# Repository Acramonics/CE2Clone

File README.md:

Boss CE-2 Clone
===============

**Andrew Martin, September 2025**

*Please note that I don't yet have this working! I believe this is a result of a bad clone MN3007!*

Introduction
------------

The Boss CE-2 is one of the best-known chorus pedals around and there
have been several clones with and without modifications. In the
`Schematics` folder, there is a collection of freely-available
schematics and information while the `Analysis` folder contains some
information on chorus effects and a full analysis of the workings of
the Boss CE-2 from ElectroSmash.

The `kicad` folder contains my schematic for a clone which is
essentially the original version with the 'anti-tic' modification and
with 2N5088 transistors throughout. Within that are two sub-folders,
`V0.1` and `V1.1`. *Do not use V0.1* - this was an erroneous design
where the inputs to the RC4558 (U1) were swapped by mistake!

V1.1 is my first correct layout with (optional) LED and (bypassable)
-ve power supply resistor and diode (see some of the schamatics and
analyses for references to this). It is a very tightly packed 57x87mm
board.

V1.2 is the current version in which the PCB layout is inspired by the
one used by Azure. This one contains the (bypassable) -ve power supply
resistor and diode, but not the LED as the intention is to use it with
my FootSwitch board. This is a somewhat less tightly packed board
(73x83mm) with wider (1mm) tracks; there was notable resistance
with the narrow tracks of V1.1.

Kicad
-----

The design uses my own symbol for the 2N5088 which is in my
`ACRM_KiCad_Libs` library.

The rate and depth pots (both are 100K linear pots) are not included
in the schematic - instead there are just positions for Molex KK254
connectors. If you wish, you can omit the connectors and wire direct
to the board.

Testing
-------

Note that the MN3007/MN3101 need a negative power supply, so it is
correct that the GND pin (Pin 1) on both is connected to the +9VA rail
and the input voltage VDD pin (Pin 3 on the MN3101 and Pin 5 on the
MN3007) is connected to GND.

Faulty (apparently they are very static sensitive, but I haven't seen
that), or bad clone, MN3101s are common, so it's a good idea to check
that it's working properly. There are three things to check in the circuit:

- Connect a meter across pins 1 (your black test lead) and 3 (red test
  lead) to find the power supply voltage you are getting. This should
  be showing a value of around -8.5V. Make sure you note what the
  exact voltage is.

- Connect a meter across pins 1 (black test lead) and 8 (VGG_OUT, red
  test lead). This should read VDD*14/15, so if your VDD was -8.5, you
  should be obtaining -7.93V.

- Put a 'scope on pin 2 (CP1) and then on pin 4 (CP2). You should see
  a (roughly) square wave form that expands and contracts. The amount
  of variation changes with the depth pot and the rate with the rate
  pot.

If those tests all work, then your MN3101 is working correctly.

Setup
-----

Turn the **Rate** pot fully **anti-clockwise** (minimum rate) and the
**Depth** pot fully **clockwise** (maximum depth).

Use a signal generator to feed a 200Hz, +3dBm sine signal into the
input. This comes from the setup information I have seen online.

+3dBm is 0.893V peak-to-peak (0.316V RMS) assuming an input impedance
of 50R. However, with the 1M Rin1 input resistor, the impedance should
be closer to 1M, and that would require an input signal of >126V
peak-to-peak (44.7V RMS)!!!

I would start with 1V peak-to-peak. Connect an oscilloscope to the
emitter of Q3 and turn the bias pot (the trimmer on the board) until
you see a center point where the sine wave is symmertrical (equally
clipped at top and bottom). If you don't see any clipping, then
increase the input sine wave voltage until you do.

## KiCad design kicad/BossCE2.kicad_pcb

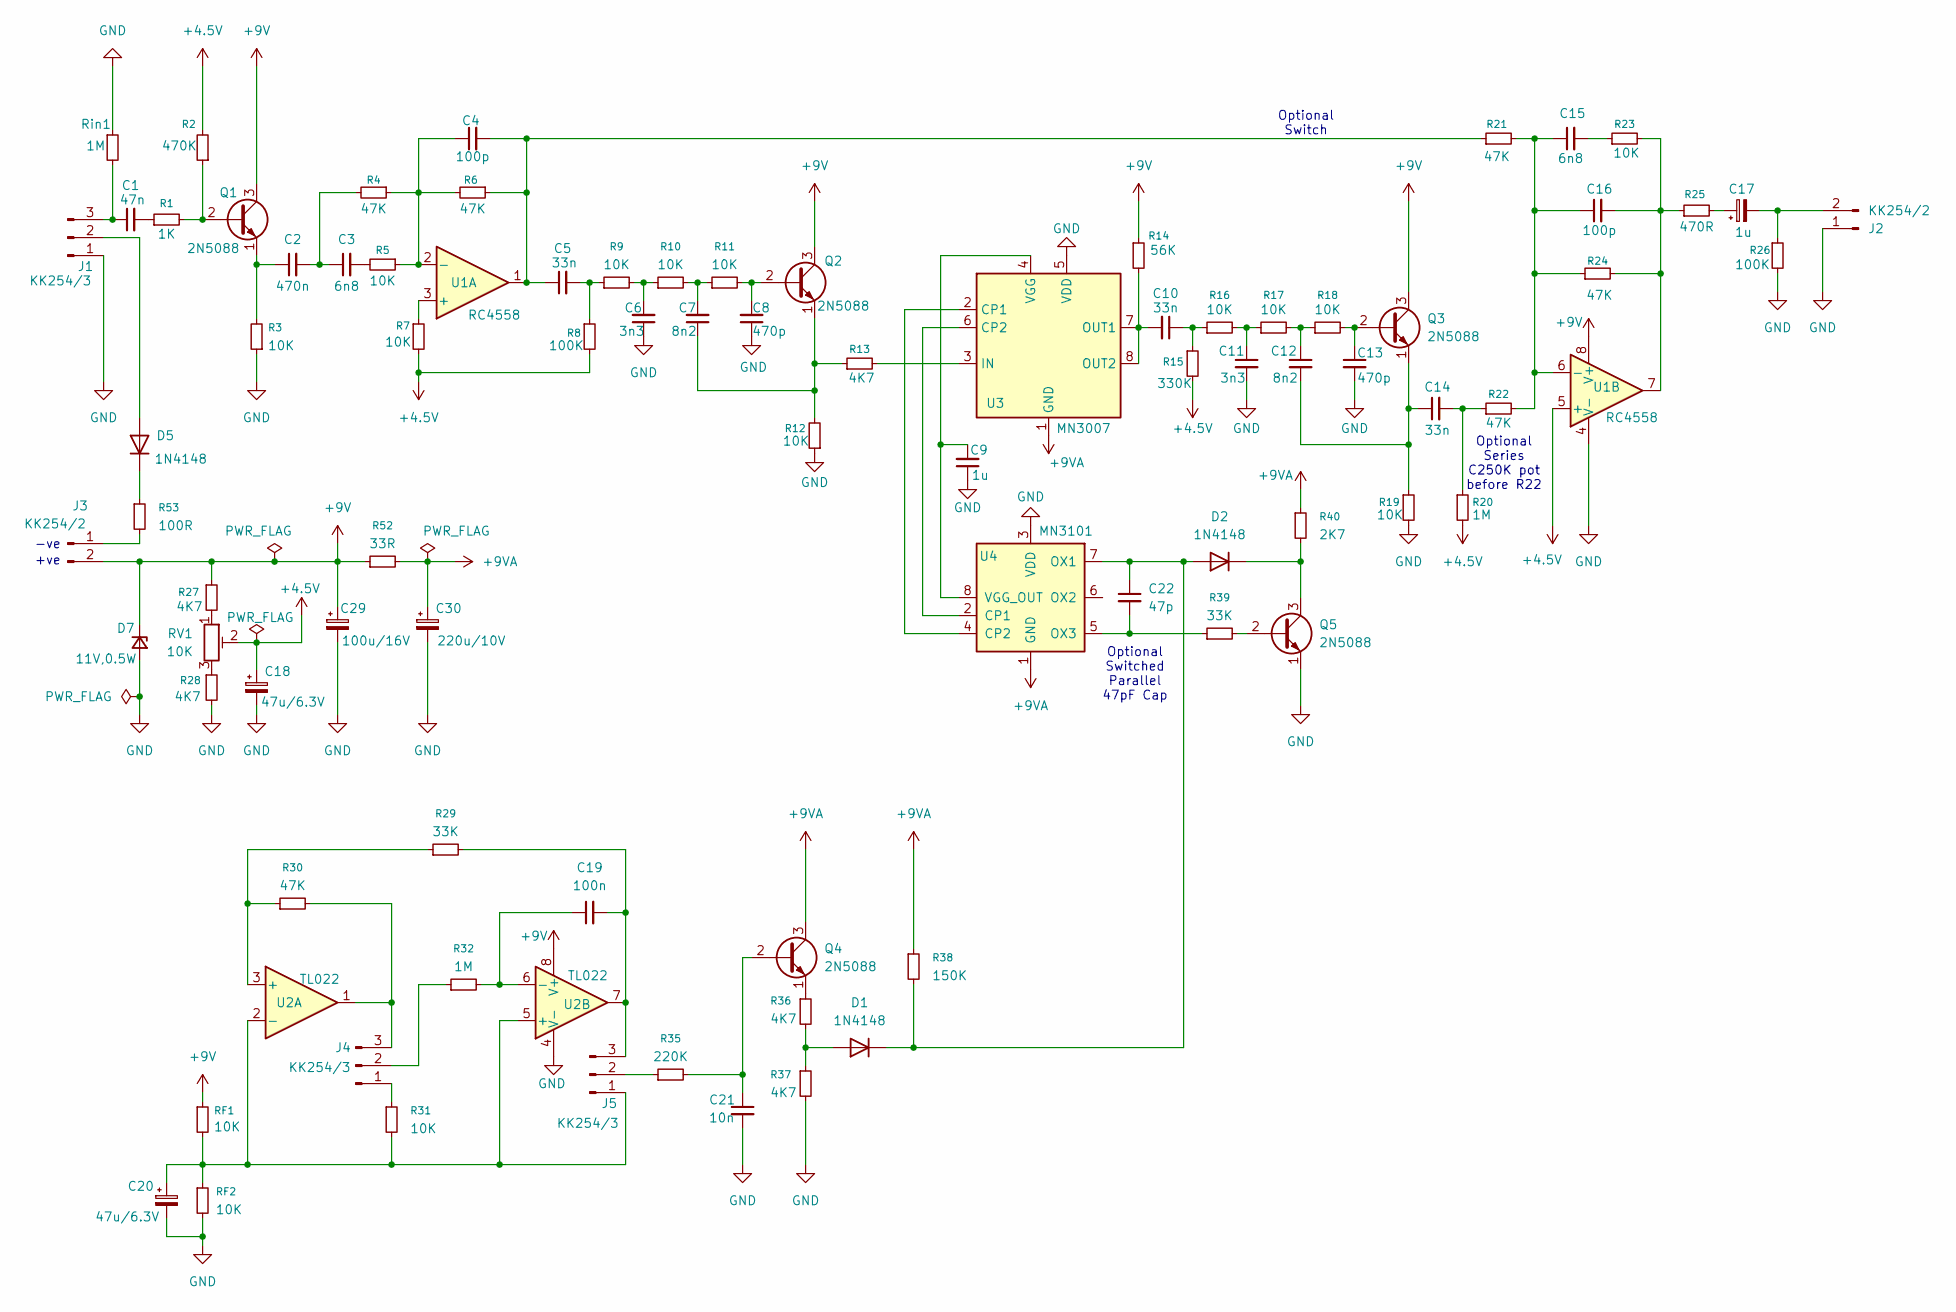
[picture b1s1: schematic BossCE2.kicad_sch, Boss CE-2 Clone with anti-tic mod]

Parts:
C1: 47n; C_Rect_L7.0mm_W2.5mm_P5.00mm
C2: 470n; C_Rect_L7.0mm_W2.5mm_P5.00mm
C3, C15: 6n8; C_Rect_L7.0mm_W2.5mm_P5.00mm
C4, C16: 100p; C_Disc_D4.3mm_W1.9mm_P5.00mm
C5, C10, C14: 33n; C_Rect_L7.0mm_W2.5mm_P5.00mm
C6, C11: 3n3; C_Rect_L7.0mm_W2.5mm_P5.00mm
C7, C12: 8n2; C_Rect_L7.0mm_W2.5mm_P5.00mm
C8, C13: 470p; C_Disc_D4.3mm_W1.9mm_P5.00mm
C9, C17: 1u; C_Rect_L7.0mm_W2.5mm_P5.00mm
C18, C20: 47u/6.3V; CP_Radial_D5.0mm_P2.50mm
C19: 100n; C_Rect_L7.0mm_W2.5mm_P5.00mm
C21: 10n; C_Disc_D4.3mm_W1.9mm_P5.00mm
C22: 47p; C_Disc_D4.3mm_W1.9mm_P5.00mm
C29: 100u/16V; CP_Radial_D5.0mm_P2.50mm
C30: 220u/10V; CP_Radial_D5.0mm_P2.50mm
D1, D2, D5: 1N4148; D_DO-35_SOD27_P7.62mm_Horizontal
D7: 11V,0.5W; D_DO-35_SOD27_P7.62mm_Horizontal
J1, J4, J5: KK254/3; Molex_KK-254_AE-6410-03A_1x03_P2.54mm_Vertical
J2, J3: KK254/2; Molex_KK-254_AE-6410-02A_1x02_P2.54mm_Vertical
Q1, Q2, Q3, Q4, Q5: 2N5088; TO-92L_HandSolder
R1: 1K; R_Axial_DIN0207_L6.3mm_D2.5mm_P10.16mm_Horizontal
R2: 470K; R_Axial_DIN0207_L6.3mm_D2.5mm_P10.16mm_Horizontal
R3, R5, R7, R9, R10, R11, R12, R16, R17, R18, R19, R23, R31: 10K; R_Axial_DIN0207_L6.3mm_D2.5mm_P10.16mm_Horizontal
R4, R6, R21, R22, R24, R30: 47K; R_Axial_DIN0207_L6.3mm_D2.5mm_P10.16mm_Horizontal
R8, R26: 100K; R_Axial_DIN0207_L6.3mm_D2.5mm_P10.16mm_Horizontal
R13, R27, R28, R36, R37: 4K7; R_Axial_DIN0207_L6.3mm_D2.5mm_P10.16mm_Horizontal
R14: 56K; R_Axial_DIN0207_L6.3mm_D2.5mm_P10.16mm_Horizontal
R15: 330K; R_Axial_DIN0207_L6.3mm_D2.5mm_P10.16mm_Horizontal
R20, R32: 1M; R_Axial_DIN0207_L6.3mm_D2.5mm_P10.16mm_Horizontal
R25: 470R; R_Axial_DIN0207_L6.3mm_D2.5mm_P10.16mm_Horizontal
R29, R39: 33K; R_Axial_DIN0207_L6.3mm_D2.5mm_P10.16mm_Horizontal
R35: 220K; R_Axial_DIN0207_L6.3mm_D2.5mm_P10.16mm_Horizontal
R38: 150K; R_Axial_DIN0207_L6.3mm_D2.5mm_P10.16mm_Horizontal
R40: 2K7; R_Axial_DIN0207_L6.3mm_D2.5mm_P10.16mm_Horizontal
R52: 33R; R_Axial_DIN0207_L6.3mm_D2.5mm_P10.16mm_Horizontal
R53: 100R; R_Axial_DIN0207_L6.3mm_D2.5mm_P10.16mm_Horizontal
RF1, RF2: 10K; R_Axial_DIN0207_L6.3mm_D2.5mm_P10.16mm_Horizontal
RV1: 10K; Potentiometer_Piher_PT-10-V05_Vertical
Rin1: 1M; R_Axial_DIN0207_L6.3mm_D2.5mm_P10.16mm_Horizontal
U1: RC4558; DIP-8_W7.62mm
U2: TL022; DIP-8_W7.62mm
U3: MN3007; DIP-8_W7.62mm
U4: MN3101; DIP-8_W7.62mm

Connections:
+4.5V: C18.1, R2.2, R7.2, R8.2, R15.2, R20.2, RV1.2, U1.5 (+)
+9V: C29.1, D7.1 (K), J3.2, Q1.3 (C), Q2.3 (C), Q3.3 (C), R14.1, R27.1, R52.1, RF1.1, U1.8 (V+), U2.8 (V+)
+9VA: C30.1, Q4.3 (C), R38.1, R40.1, R52.2, U3.1 (GND), U4.1 (GND)
GND: C6.1, C8.1, C9.1, C11.2, C13.2, C18.2, C20.2, C21.2, C29.2, C30.2, D7.2 (A), J1.1, J2.1, Q5.1 (E), R3.1, R12.1, R19.2, R26.2, R28.2, R37.2, RF2.2, Rin1.1, U1.4 (V-), U2.4 (V-), U3.5 (VDD), U4.3 (VDD)
unnamed: C1.2, R1.1
unnamed: C2.2, C3.1, R4.2
unnamed: C3.2, R5.2
unnamed: C4.2, C5.1, R6.1, R21.1, U1.1
unnamed: C5.2, R8.1, R9.1
unnamed: C6.2, R9.2, R10.1
unnamed: C7.2, R10.2, R11.1
unnamed: C10.1, R15.1, R16.1
unnamed: C11.1, R16.2, R17.1
unnamed: C12.1, R17.2, R18.1
unnamed: C14.2, R20.1, R22.1
unnamed: C15.2, R23.1
unnamed: C16.2, R23.2, R24.2, R25.1, U1.7
unnamed: C17.1, R25.2
unnamed: D1.2 (A), R36.2, R37.1
unnamed: C22.1, D1.1 (K), D2.2 (A), R38.2, U4.7 (OX1)
unnamed: D2.1 (K), Q5.3 (C), R40.2
unnamed: D5.2 (A), J1.2
unnamed: D5.1 (K), R53.1
unnamed: C1.1, J1.3, Rin1.2
unnamed: C17.2, J2.2, R26.1
unnamed: J3.1, R53.2
unnamed: J4.1, R31.1
unnamed: J4.2, R32.1
unnamed: J4.3, R30.2, U2.1
unnamed: C20.1, J5.1, R31.2, RF1.2, RF2.1, U2.2 (-), U2.5 (+)
unnamed: J5.2, R35.1
unnamed: C19.2, J5.3, R29.2, U2.7
unnamed: Q1.2 (B), R1.2, R2.1
unnamed: C2.1, Q1.1 (E), R3.2
unnamed: C8.2, Q2.2 (B), R11.2
unnamed: C7.1, Q2.1 (E), R12.2, R13.1
unnamed: C13.1, Q3.2 (B), R18.2
unnamed: C12.2, C14.1, Q3.1 (E), R19.1
unnamed: C21.1, Q4.2 (B), R35.2
unnamed: Q4.1 (E), R36.1
unnamed: Q5.2 (B), R39.2
unnamed: R27.2, RV1.1
unnamed: R28.1, RV1.3
unnamed: R7.1, U1.3 (+)
unnamed: C4.1, R4.1, R5.1, R6.2, U1.2 (-)
unnamed: C15.1, C16.1, R21.2, R22.2, R24.1, U1.6 (-)
unnamed: R29.1, R30.1, U2.3 (+)
unnamed: C19.1, R32.2, U2.6 (-)
unnamed: U3.2 (CP1), U4.4 (CP2)
unnamed: U3.6 (CP2), U4.2 (CP1)
unnamed: R13.2, U3.3 (IN)
unnamed: C10.2, R14.2, U3.7 (OUT1), U3.8 (OUT2)
unnamed: C9.2, U3.4 (VGG), U4.8 (VGG_OUT)
unnamed: C22.2, R39.1, U4.5 (OX3)

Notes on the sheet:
+ve
Optional Series C250K pot before R22
Optional Switched Parallel 47pF Cap
Optional Switch
-ve

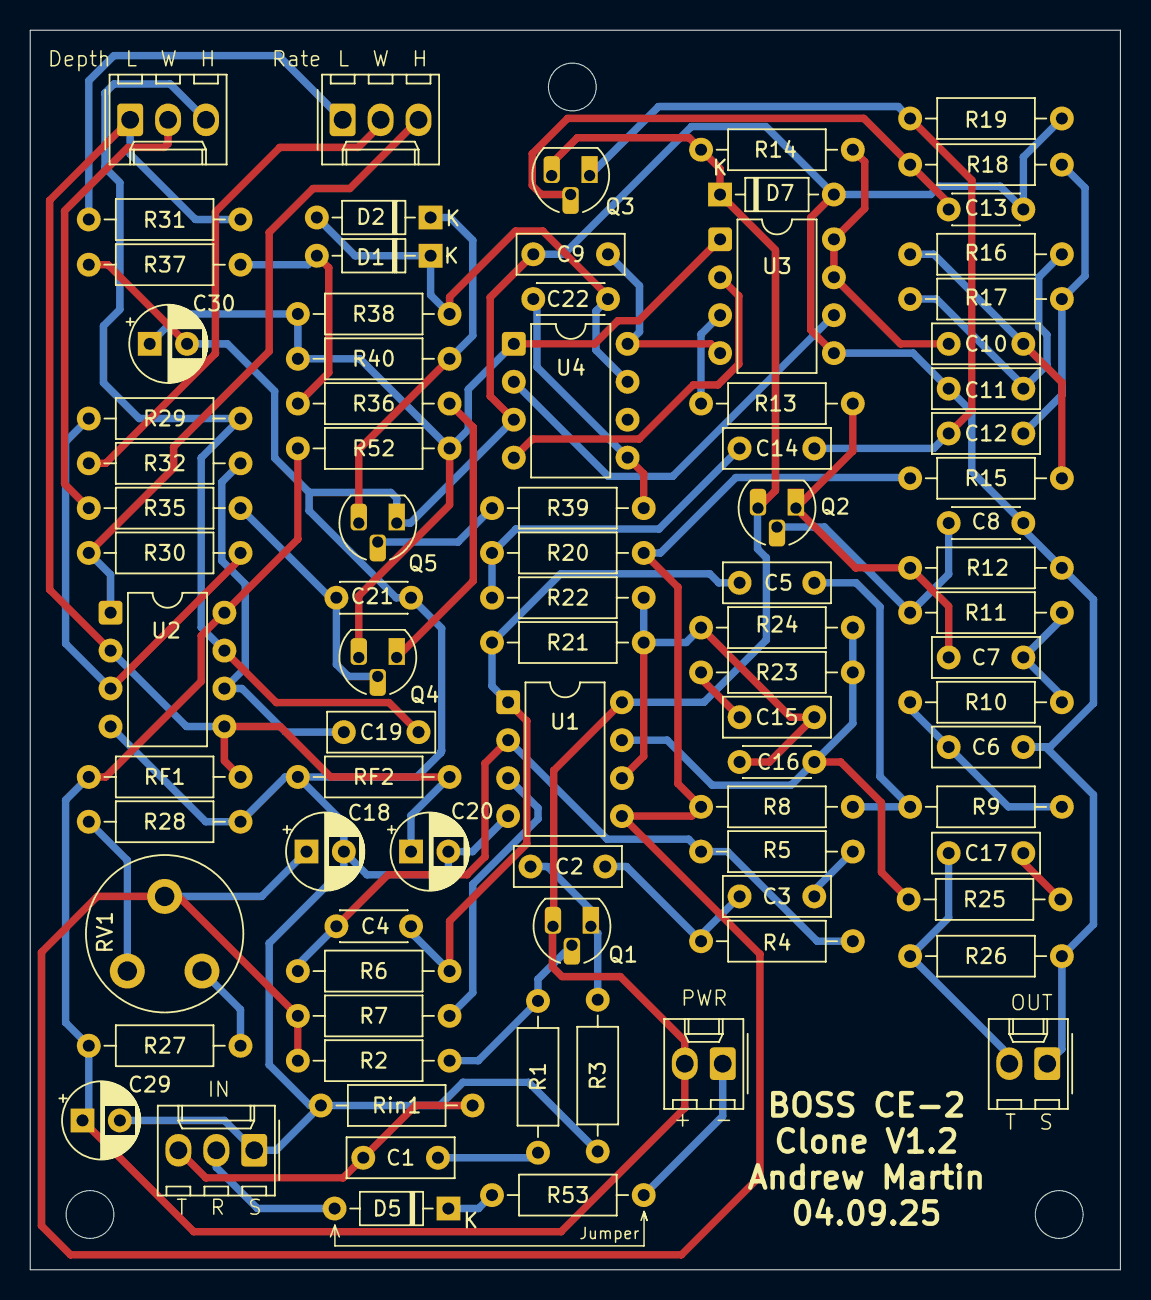
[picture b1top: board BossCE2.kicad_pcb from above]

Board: 2 copper layers, 73.0 x 83.0 mm, 86 parts (0 on the bottom side), 54 nets.
